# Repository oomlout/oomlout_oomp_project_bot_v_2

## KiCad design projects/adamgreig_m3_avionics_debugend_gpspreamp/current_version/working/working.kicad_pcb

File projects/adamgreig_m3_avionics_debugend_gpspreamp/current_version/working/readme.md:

# m3_avionics
 
## summary 
* id: adamgreig_m3_avionics_debugend_gpspreamp
* user: adamgreig
* name: m3_avionics
* board: debugend_gpspreamp
* repo: https://github.com/adamgreig/m3-avionics
* src_file_repo_kicad_pcb: m3debug/end_pcb/panel_with_gpspreamp/debugend_gpspreamp.kicad_pcb
* src_file_repo_kicad_pcb_link: https://github.com/adamgreig/m3-avionics/tree/master/m3debug/end_pcb/panel_with_gpspreamp/debugend_gpspreamp.kicad_pcb

* src_file_repo_sch: m3debug/end_pcb/m3debug_end.sch
* src_file_repo_sch_link: https://github.com/adamgreig/m3-avionics/tree/master/m3debug/end_pcb/m3debug_end.sch
* full details link: https://github.com/oomlout/oomlout_oomp_project_bot_v_2/tree/main/projects/adamgreig_m3_avionics_debugend_gpspreamp/current_version/working  

## pcb  

[board (pdf)](working.pdf)  

## working_bom
| Id | Designator | Footprint | Quantity | Designation | Supplier and ref |  | None | 
| --- | --- | --- | --- | --- | --- | --- | --- | 
| 1 | J1 | TFML-110-02-L-D | 1 | WEST TOP |  |  | [''] | 
| 2 | J2 | TFML-110-02-L-D | 1 | EAST TOP |  |  | [''] | 
| 3 | R1 | 0402 | 1 | 120 |  |  | [''] | 
| 4 | J5,J6,J7,J8 | SIL-254P-10 | 4 | CONN_01x10 |  |  | [''] | 
| 5 | C1 | 0402 | 1 | 1Âµ |  |  | [''] | 
| 6 | C2 | 0402 | 1 | 100n |  |  | [''] | 
| 7 | C3 | 0402 | 1 | 200p |  |  | [''] | 
| 8 | IC1 | DFN-6-EP-BGM | 1 | BGM1043N7 |  |  | [''] | 
| 9 | L1 | 0402 | 1 | 9n1 |  |  | [''] | 
| 10 | L2 | 0402 | 1 | 8n2 |  |  | [''] | 
| 11 | L3,L4,L5 | 0402 | 3 | 92n |  |  | [''] | 
| 12 | P2 | SMA-PTH | 1 | ANTENNA |  |  | [''] | 
| 13 | P3 | SMA-EDGE | 1 | RECEIVER |  |  | [''] | 
| 14 | J3 | SFML-110-02-L-D-LC | 1 | WEST BOT |  |  | [''] | 
| 15 | J4 | SFML-110-02-L-D-LC | 1 | EAST BOT |  |  | [''] |

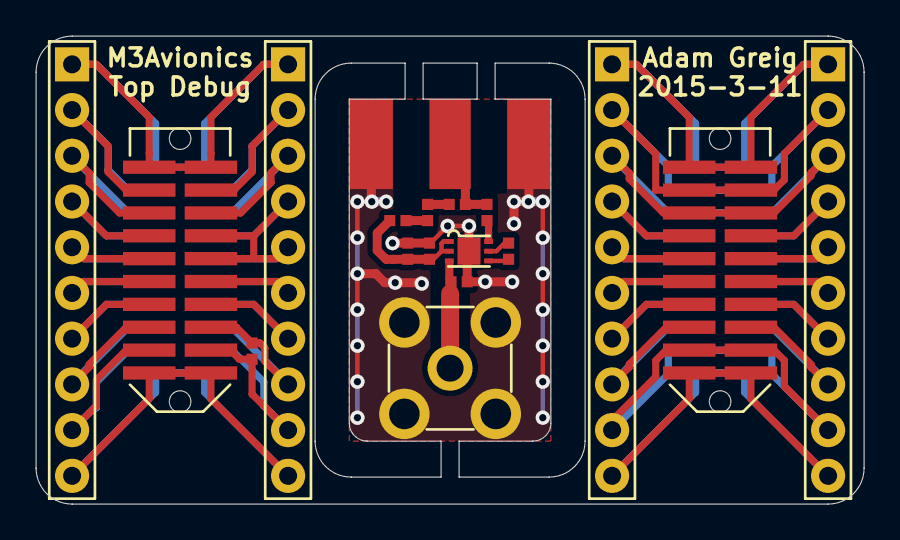
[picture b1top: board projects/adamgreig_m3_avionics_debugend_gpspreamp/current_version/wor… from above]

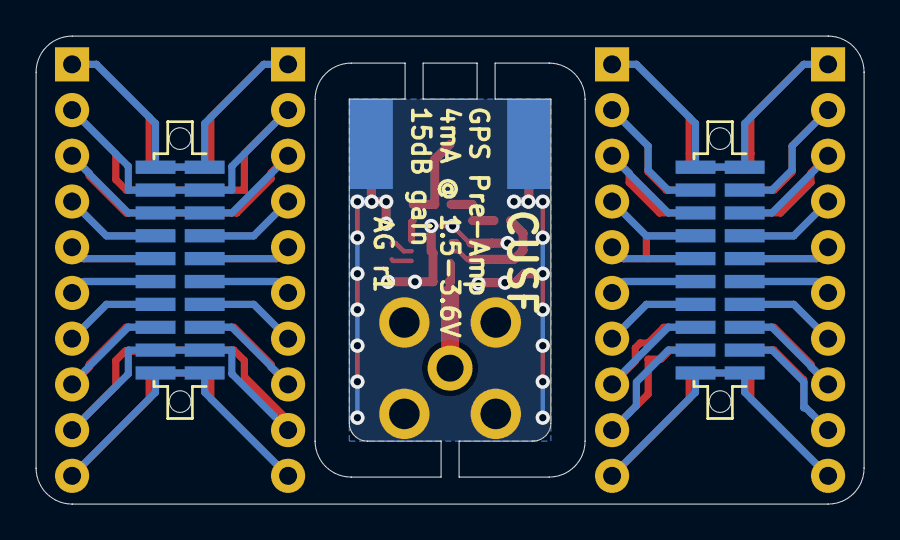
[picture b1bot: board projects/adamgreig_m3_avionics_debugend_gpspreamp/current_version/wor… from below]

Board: 2 copper layers, 46.0 x 26.0 mm, 20 parts (2 on the bottom side), 37 nets.

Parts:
C1: 1µ; 0402
C2: 100n; 0402
C3: 200p; 0402
IC1: BGM1043N7; DFN-6-EP-BGM
J1: WEST TOP; TFML-110-02-L-D
J2: EAST TOP; TFML-110-02-L-D
J3: WEST BOT; SFML-110-02-L-D-LC
J4: EAST BOT; SFML-110-02-L-D-LC
J5, J6, J7, J8: CONN_01x10; SIL-254P-10
L1: 9n1; 0402
L2: 8n2; 0402
L3, L4, L5: 92n; 0402
P2: ANTENNA; SMA-PTH
P3: RECEIVER; SMA-EDGE
R1: 120; 0402

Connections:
/3v3_AUX1: J1.13, J3.13, J5.7
/3v3_AUX2: J1.15, J3.15, J5.8
/3v3_DL: J1.11, J3.11, J5.6
/3v3_FC: J1.7, J3.7, J5.4
/3v3_IMU: J1.3, J3.3, J5.2
/3v3_PYRO: J1.9, J3.9, J5.5
/3v3_RADIO: J1.5, J3.5, J5.3
/5v_AUX1: J2.11, J4.11, J7.6
/5v_AUX2: J2.13, J4.13, J7.7
/5v_CAM: J2.15, J4.15, J7.8
/5v_CAN: J1.14, J3.14, J6.7
/5v_IMU: J2.9, J4.9, J7.5
/5v_RADIO: J2.7, J4.7, J7.4
/CAN+: J1.18, J3.18, J6.9, R1.1
/CAN-: J1.16, J3.16, J6.8, R1.2
/CHARGE: J2.17, J2.18, J4.17, J4.18, J7.9, J8.9
/JTCK: J1.6, J3.6, J6.3
/JTDI: J1.8, J1.10, J3.8, J3.10, J6.4, J6.5
/JTMS: J1.4, J3.4, J6.2
/PWR: J2.16, J4.16, J8.8
/PYRO1: J2.8, J4.8, J8.4
/PYRO2: J2.10, J4.10, J8.5
/PYRO3: J2.12, J4.12, J8.6
/PYRO4: J2.14, J4.14, J8.7
/PYRO_SI: J2.5, J2.6, J4.5, J4.6, J7.3, J8.3
/PYRO_SO: J2.3, J2.4, J4.3, J4.4, J7.2, J8.2
/RSVD1: J1.12, J3.12, J6.6
/RSVD2: J1.17, J3.17, J5.9
GND: C1.2, C2.2, IC1.EP, J1.1, J1.2, J1.19, J1.20, J2.1, J2.2, J2.19, J2.20, J3.1, J3.2, J3.19, J3.20, J4.1, J4.2, J4.19, J4.20, J5.1, J5.10, J6.1, J6.10, J7.1, J7.10, J8.1, J8.10, L1.2, P2.2, P3.2
unnamed: C1.1, C2.1, IC1.1, IC1.2, L3.1
unnamed: C3.1, IC1.6
unnamed: C3.2, L5.2, P3.1
unnamed: IC1.3, L1.1, P2.1
unnamed: IC1.4, L2.1
unnamed: IC1.5, L2.2
unnamed: L3.2, L4.1
unnamed: L4.2, L5.1

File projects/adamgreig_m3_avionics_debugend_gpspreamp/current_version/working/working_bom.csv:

"Id";"Designator";"Footprint";"Quantity";"Designation";"Supplier and ref";
1;"J1";"TFML-110-02-L-D";1;"WEST TOP";;;
2;"J2";"TFML-110-02-L-D";1;"EAST TOP";;;
3;"R1";"0402";1;"120";;;
4;"J5,J6,J7,J8";"SIL-254P-10";4;"CONN_01x10";;;
5;"C1";"0402";1;"1µ";;;
6;"C2";"0402";1;"100n";;;
7;"C3";"0402";1;"200p";;;
8;"IC1";"DFN-6-EP-BGM";1;"BGM1043N7";;;
9;"L1";"0402";1;"9n1";;;
10;"L2";"0402";1;"8n2";;;
11;"L3,L4,L5";"0402";3;"92n";;;
12;"P2";"SMA-PTH";1;"ANTENNA";;;
13;"P3";"SMA-EDGE";1;"RECEIVER";;;
14;"J3";"SFML-110-02-L-D-LC";1;"WEST BOT";;;
15;"J4";"SFML-110-02-L-D-LC";1;"EAST BOT";;;

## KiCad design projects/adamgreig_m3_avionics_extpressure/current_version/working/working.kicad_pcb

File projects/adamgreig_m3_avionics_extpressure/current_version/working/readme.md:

# m3_avionics
 
## summary 
* id: adamgreig_m3_avionics_extpressure
* user: adamgreig
* name: m3_avionics
* board: extpressure
* repo: https://github.com/adamgreig/m3-avionics
* src_file_repo_kicad_pcb: m3dl/extpressure/extpressure.kicad_pcb
* src_file_repo_kicad_pcb_link: https://github.com/adamgreig/m3-avionics/tree/master/m3dl/extpressure/extpressure.kicad_pcb

* src_file_repo_sch: m3dl/extpressure/extpressure.sch
* src_file_repo_sch_link: https://github.com/adamgreig/m3-avionics/tree/master/m3dl/extpressure/extpressure.sch
* full details link: https://github.com/oomlout/oomlout_oomp_project_bot_v_2/tree/main/projects/adamgreig_m3_avionics_extpressure/current_version/working  

## schematic  
  
[schematic (pdf)](working_schematic.pdf) 

## pcb  

[board (pdf)](working.pdf)  

## working_bom
| Id | Designator | Footprint | Quantity | Designation | Supplier and ref |  | None | 
| --- | --- | --- | --- | --- | --- | --- | --- | 
| 1 | P1 | TC2030-NL | 1 | SWD_TC |  |  | [''] | 
| 2 | IC1,IC4,IC3,IC2 | SP100 | 4 | SP100 |  |  | [''] | 
| 3 | J1 | S04B-PASK-2 | 1 | SERIAL |  |  | [''] | 
| 4 | IC5 | LQFP-32 | 1 | STM32F0xxKxTx |  |  | [''] | 
| 5 | D1 | 0603-LED | 1 | RED |  |  | [''] | 
| 6 | C3,C4,C1,C6,C7,C2 | 0402 | 6 | 100n |  |  | [''] | 
| 7 | C5 | 0402 | 1 | 4Âµ7 |  |  | [''] | 
| 8 | C8 | 0402 | 1 | 1Âµ |  |  | [''] | 
| 9 | C9 | 0402 | 1 | 10n |  |  | [''] | 
| 10 | R1,R2 | 0402 | 2 | 1k |  |  | [''] | 
| 11 | D2 | 0603-LED | 1 | GRN |  |  | [''] | 
| 12 | REF**,REF**,REF**,REF** | M3_MOUNT | 4 | M3_MOUNT |  |  | [''] | 
| 13 | D4,D5,D3 | 0402 | 3 | ESD_DIODE |  |  | [''] | 

## bom_schematic
| Ref | Qnty | Value | Cmp name | Footprint | Description | Vendor | DNP | 
| --- | --- | --- | --- | --- | --- | --- | --- | 
| C1, C2, C3, C4, C6, C7 | 6 | 100n | C | agg:0402 |  |  |  | 
| C5 | 1 | 4Âµ7 | C | agg:0402 |  |  |  | 
| C8 | 1 | 1Âµ | C | agg:0402 |  |  |  | 
| C9 | 1 | 10n | C | agg:0402 |  |  |  | 
| D1 | 1 | RED | LED | agg:0603-LED |  |  |  | 
| D2 | 1 | GRN | LED | agg:0603-LED |  |  |  | 
| D3, D4, D5 | 3 | ESD_DIODE | ESD_DIODE | agg:0402 |  |  |  | 
| IC1, IC2, IC3, IC4 | 4 | SP100 | SP100 | agg:SP100 |  |  |  | 
| IC5 | 1 | STM32F0xxKxTx | STM32F0xxKxTx | agg:LQFP-32 |  |  |  | 
| J1 | 1 | SERIAL | CONN_01x04 | agg:S04B-PASK-2 |  |  |  | 
| P1 | 1 | SWD_TC | SWD_TC | agg:TC2030-NL |  |  |  | 
| R1, R2 | 2 | 1k | R | agg:0402 |  |  |  |

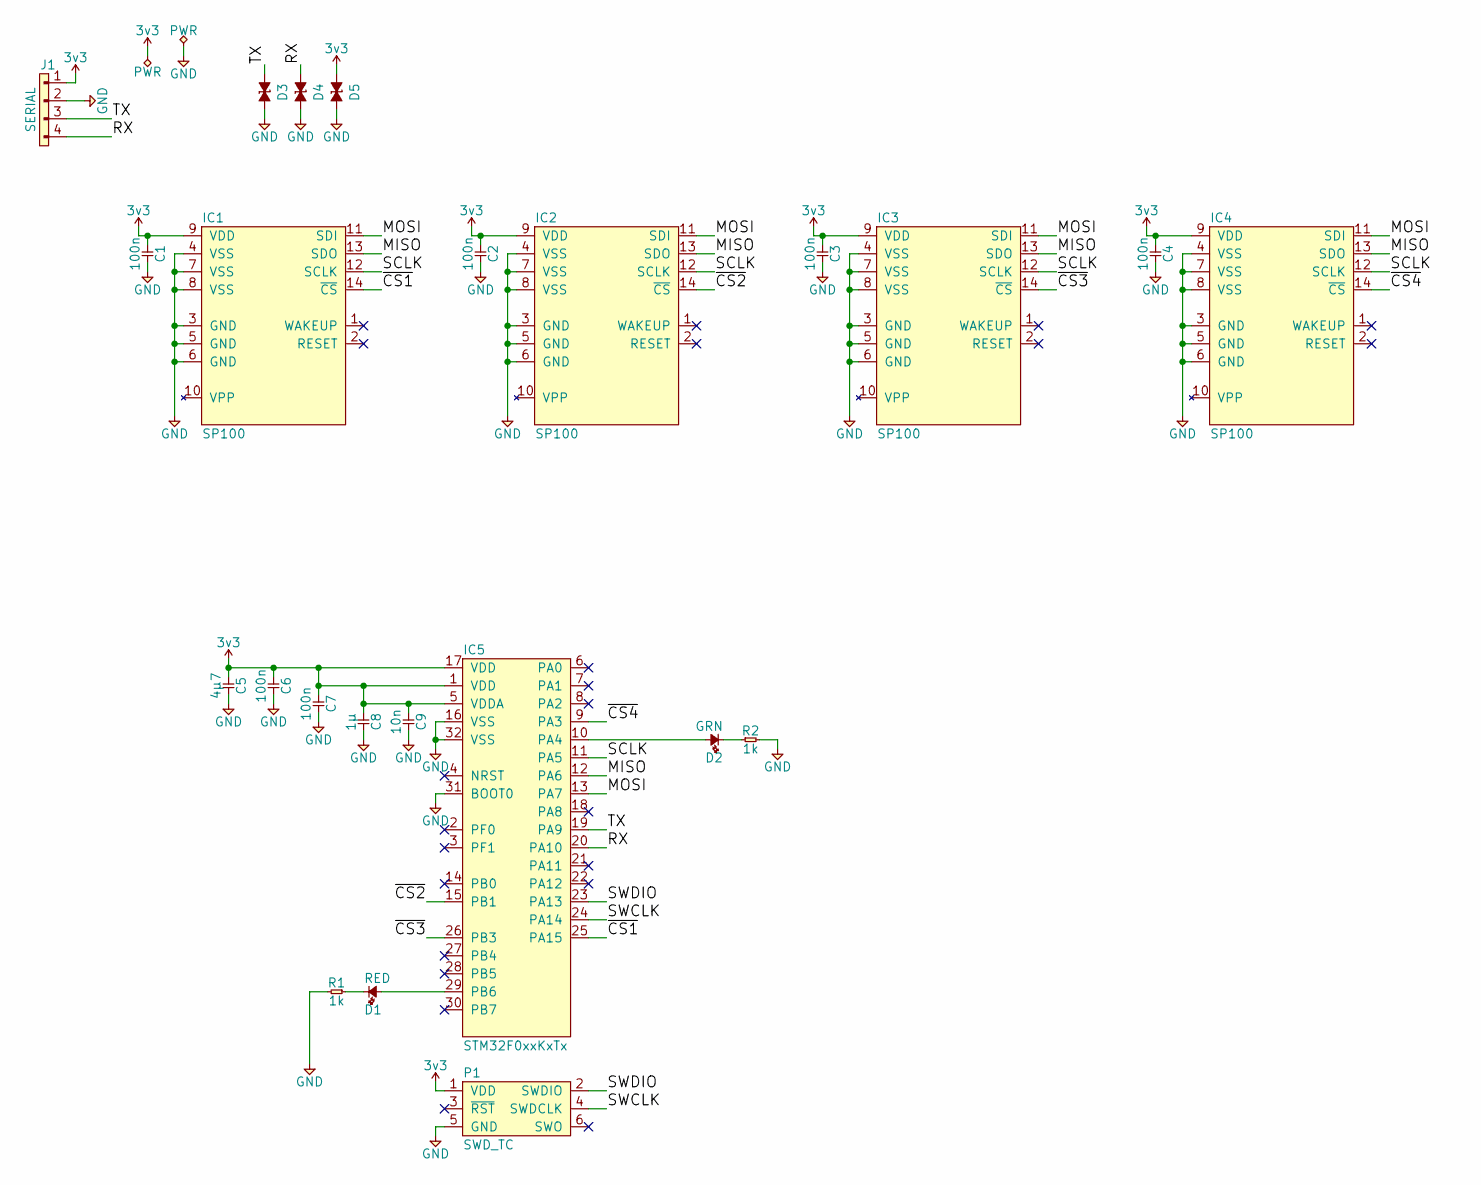
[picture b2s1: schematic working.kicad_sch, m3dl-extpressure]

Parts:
C1, C2, C3, C4, C6, C7: 100n; 0402; Farnell 2496771
C5: 4µ7; 0402; Farnell 2426952
C8: 1µ; 0402; Farnell 2496814
C9: 10n; 0402; Farnell 2210793
D1: RED; 0603-LED; Farnell 2290329
D2: GRN; 0603-LED; Farnell 2290328
D3, D4, D5: ESD_DIODE; 0402; Farnell 2368169
IC1, IC2, IC3, IC4: SP100; Farnell 1845345
IC5: STM32F0xxKxTx; LQFP-32; Farnell 2333141
J1: SERIAL; S04B-PASK-2; Farnell 1830749
P1: SWD_TC; TC2030-NL
R1, R2: 1k; 0402; Farnell 2447120

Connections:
3v3: C1.1, C2.1, C3.1, C4.1, C5.1, C6.1, C7.1, C8.1, C9.1, D5.1, IC1.9 (VDD), IC2.9 (VDD), IC3.9 (VDD), IC4.9 (VDD), IC5.1 (VDD), IC5.5 (VDDA), IC5.17 (VDD), J1.1, P1.1 (VDD)
/MISO: IC1.13 (SDO), IC2.13 (SDO), IC3.13 (SDO), IC4.13 (SDO), IC5.12 (PA6)
/MOSI: IC1.11 (SDI), IC2.11 (SDI), IC3.11 (SDI), IC4.11 (SDI), IC5.13 (PA7)
/RX: D4.1, IC5.20 (PA10), J1.4
/SCLK: IC1.12 (SCLK), IC2.12 (SCLK), IC3.12 (SCLK), IC4.12 (SCLK), IC5.11 (PA5)
/SWCLK: IC5.24 (PA14), P1.4 (SWDCLK)
/SWDIO: IC5.23 (PA13), P1.2 (SWDIO)
/TX: D3.1, IC5.19 (PA9), J1.3
/~CS1: IC1.14 (~CS), IC5.25 (PA15)
/~CS2: IC2.14 (~CS), IC5.15 (PB1)
/~CS3: IC3.14 (~CS), IC5.26 (PB3)
/~CS4: IC4.14 (~CS), IC5.9 (PA3)
GND: C1.2, C2.2, C3.2, C4.2, C5.2, C6.2, C7.2, C8.2, C9.2, D3.2, D4.2, D5.2, IC1.3 (GND), IC1.4 (VSS), IC1.5 (GND), IC1.6 (GND), IC1.7 (VSS), IC1.8 (VSS), IC2.3 (GND), IC2.4 (VSS), IC2.5 (GND), IC2.6 (GND), IC2.7 (VSS), IC2.8 (VSS), IC3.3 (GND), IC3.4 (VSS), IC3.5 (GND), IC3.6 (GND), IC3.7 (VSS), IC3.8 (VSS), IC4.3 (GND), IC4.4 (VSS), IC4.5 (GND), IC4.6 (GND), IC4.7 (VSS), IC4.8 (VSS), IC5.16 (VSS), IC5.31 (BOOT0), IC5.32 (VSS), J1.2, P1.5 (GND), R1.2, R2.2
unnamed: D1.1, R1.1
unnamed: D1.2, IC5.29 (PB6)
unnamed: D2.1, R2.1
unnamed: D2.2, IC5.10 (PA4)

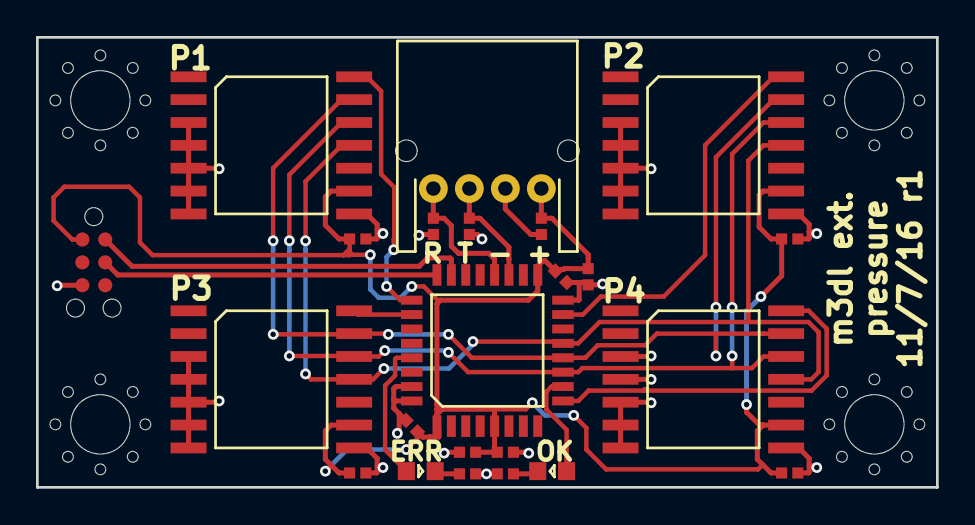
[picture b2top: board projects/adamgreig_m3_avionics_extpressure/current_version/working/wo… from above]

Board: 2 copper layers, 50.0 x 25.0 mm, 23 parts (0 on the bottom side), 17 nets.

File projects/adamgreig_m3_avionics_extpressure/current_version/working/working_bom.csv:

"Id";"Designator";"Footprint";"Quantity";"Designation";"Supplier and ref";
1;"P1";"TC2030-NL";1;"SWD_TC";;;
2;"IC1,IC4,IC3,IC2";"SP100";4;"SP100";;;
3;"J1";"S04B-PASK-2";1;"SERIAL";;;
4;"IC5";"LQFP-32";1;"STM32F0xxKxTx";;;
5;"D1";"0603-LED";1;"RED";;;
6;"C3,C4,C1,C6,C7,C2";"0402";6;"100n";;;
7;"C5";"0402";1;"4µ7";;;
8;"C8";"0402";1;"1µ";;;
9;"C9";"0402";1;"10n";;;
10;"R1,R2";"0402";2;"1k";;;
11;"D2";"0603-LED";1;"GRN";;;
12;"REF**,REF**,REF**,REF**";"M3_MOUNT";4;"M3_MOUNT";;;
13;"D4,D5,D3";"0402";3;"ESD_DIODE";;;

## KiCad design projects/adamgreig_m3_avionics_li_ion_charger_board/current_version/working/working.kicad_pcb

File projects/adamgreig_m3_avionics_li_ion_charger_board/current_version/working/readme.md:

# m3_avionics
 
## summary 
* id: adamgreig_m3_avionics_li_ion_charger_board
* user: adamgreig
* name: m3_avionics
* board: li_ion_charger_board
* repo: https://github.com/adamgreig/m3-avionics
* src_file_repo_kicad_pcb: m3psu/pcb/Li-Ion-Charger-Board/Li-Ion-Charger-Board.kicad_pcb
* src_file_repo_kicad_pcb_link: https://github.com/adamgreig/m3-avionics/tree/master/m3psu/pcb/Li-Ion-Charger-Board/Li-Ion-Charger-Board.kicad_pcb

* src_file_repo_sch: m3psu/pcb/Li-Ion-Charger-Board/Li-Ion-Charger-Board.sch
* src_file_repo_sch_link: https://github.com/adamgreig/m3-avionics/tree/master/m3psu/pcb/Li-Ion-Charger-Board/Li-Ion-Charger-Board.sch
* full details link: https://github.com/oomlout/oomlout_oomp_project_bot_v_2/tree/main/projects/adamgreig_m3_avionics_li_ion_charger_board/current_version/working  

## schematic  
  
[schematic (pdf)](working_schematic.pdf) 

## pcb  

[board (pdf)](working.pdf)  

## working_bom
| Id | Designator | Footprint | Quantity | Designation | Supplier and ref |  | None | 
| --- | --- | --- | --- | --- | --- | --- | --- | 
| 1 | J1 | TFML-110-02-L-D | 1 | WEST TOP |  |  | [''] | 
| 2 | J4 | TFML-110-02-L-D | 1 | EAST TOP |  |  | [''] | 
| 3 | J3 | SIL-254P-01 | 1 | TAP |  |  | [''] | 
| 4 | J7 | SIL-254P-01 | 1 | BAT+ |  |  | [''] | 
| 5 | J8 | SIL-254P-01 | 1 | BAT- |  |  | [''] | 
| 6 | C1,C2,C8,C10,C11,C14,C15,C16,C17 | 0402 | 9 | 100n |  |  | [''] | 
| 7 | C3,C13 | 0402 | 2 | 1Âµ |  |  | [''] | 
| 8 | C4,C7 | 0805 | 2 | 2Âµ2 |  |  | [''] | 
| 9 | C5,C6,C18,C19 | 1210 | 4 | 10Âµ |  |  | [''] | 
| 10 | C9 | 0603 | 1 | 1Âµ5 |  |  | [''] | 
| 11 | C12 | 0402 | 1 | 100p |  |  | [''] | 
| 12 | C20 | 0402 | 1 | 22p |  |  | [''] | 
| 13 | D3,D4 | SOD-323 | 2 | SCHOTTKY |  |  | [''] | 
| 14 | IC1 | QFN-32-EP-TI | 1 | BQ40Z60 |  |  | [''] | 
| 15 | L1 | SRP5030T | 1 | 2Âµ2 |  |  | [''] | 
| 16 | Q1 | PowerFLAT-5x6 | 1 | NFET2 |  |  | [''] | 
| 17 | Q2 | SOT-883-B | 1 | NFET |  |  | [''] | 
| 18 | Q4 | PowerPair-3x3 | 1 | SiZ340DT |  |  | [''] | 
| 19 | R1 | 0402 | 1 | 10K |  |  | [''] | 
| 20 | R2,R7,R9 | 0402 | 3 | 10M |  |  | [''] | 
| 21 | R3,R4,R8 | 0402 | 3 | 5K1 |  |  | [''] | 
| 22 | R10,R11,R15,R16 | 0402 | 4 | 100R |  |  | [''] | 
| 23 | R12 | 0402 | 1 | 100K |  |  | [''] | 
| 24 | R13 | 0402 | 1 | 2R |  |  | [''] | 
| 25 | R14,R19 | 0402 | 2 | 10R |  |  | [''] | 
| 26 | R17 | 0805 | 1 | 5m |  |  | [''] | 
| 27 | R18 | 0603 | 1 | 10m |  |  | [''] | 
| 28 | R20 | 0402 | 1 | 330K |  |  | [''] | 
| 29 | R21 | 0402 | 1 | 56K2 |  |  | [''] | 
| 30 | Q3 | SON2x2N | 1 | NFET_GDS |  |  | [''] | 
| 31 | J2 | SFML-110-02-L-D-LC | 1 | WEST BOT |  |  | [''] | 
| 32 | J5 | SFML-110-02-L-D-LC | 1 | EAST BOT |  |  | [''] | 
| 33 | J6 | SFML-105-02-L-D-LC | 1 | NORTH BOT |  |  | [''] | 

## bom_schematic
| Ref | Qnty | Value | Cmp name | Footprint | Description | Vendor | DNP | 
| --- | --- | --- | --- | --- | --- | --- | --- | 
| C1, C2, C8, C10, C11, C14, C15, C16, C17 | 9 | 100n | C | agg:0402 |  |  |  | 
| C3, C13 | 2 | 1Âµ | C | agg:0402 |  |  |  | 
| C4, C7 | 2 | 2Âµ2 | C | agg:0805 |  |  |  | 
| C5, C6, C18, C19 | 4 | 10Âµ | C | agg:1210 |  |  |  | 
| C9 | 1 | 1Âµ5 | C | agg:0603 |  |  |  | 
| C12 | 1 | 100p | C | agg:0402 |  |  |  | 
| C20 | 1 | 22p | C | agg:0402 |  |  |  | 
| D3, D4 | 2 | SCHOTTKY | SCHOTTKY | agg:SOD-323 |  |  |  | 
| IC1 | 1 | BQ40Z60 | BQ40Z60 | agg:QFN-32-EP-TI |  |  |  | 
| J1 | 1 | WEST TOP | CONN_02x10 | agg:TFML-110-02-L-D |  |  |  | 
| J2 | 1 | WEST BOT | CONN_02x10 | agg:SFML-110-02-L-D-LC |  |  |  | 
| J3 | 1 | TAP | CONN_01x01 | agg:SIL-254P-01 |  |  |  | 
| J4 | 1 | EAST TOP | CONN_02x10 | agg:TFML-110-02-L-D |  |  |  | 
| J5 | 1 | EAST BOT | CONN_02x10 | agg:SFML-110-02-L-D-LC |  |  |  | 
| J6 | 1 | NORTH BOT | CONN_02x05 | agg:SFML-105-02-L-D-LC |  |  |  | 
| J7 | 1 | BAT+ | CONN_01x01 | agg:SIL-254P-01 |  |  |  | 
| J8 | 1 | BAT- | CONN_01x01 | agg:SIL-254P-01 |  |  |  | 
| L1 | 1 | 2Âµ2 | L | agg:SRP5030T |  |  |  | 
| Q1 | 1 | NFET2 | NFET2 | agg:PowerFLAT-5x6 |  |  |  | 
| Q2 | 1 | NFET | NFET_GDS | agg:SOT-883-B |  |  |  | 
| Q3 | 1 | NFET_GDS | NFET_GDS | agg:SON2x2N |  |  |  | 
| Q4 | 1 | SiZ340DT | SiZ340DT | agg:PowerPair-3x3 |  |  |  | 
| R1 | 1 | 10K | R | agg:0402 |  |  |  | 
| R2, R7, R9 | 3 | 10M | R | agg:0402 |  |  |  | 
| R3, R4, R8 | 3 | 5K1 | R | agg:0402 |  |  |  | 
| R10, R11, R15, R16 | 4 | 100R | R | agg:0402 |  |  |  | 
| R12 | 1 | 100K | R | agg:0402 |  |  |  | 
| R13 | 1 | 2R | R | agg:0402 |  |  |  | 
| R14, R19 | 2 | 10R | R | agg:0402 |  |  |  | 
| R17 | 1 | 5m | R | agg:0805 |  |  |  | 
| R18 | 1 | 10m | R | agg:0603 |  |  |  | 
| R20 | 1 | 330K | R | agg:0402 |  |  |  | 
| R21 | 1 | 56K2 | R | agg:0402 |  |  |  |

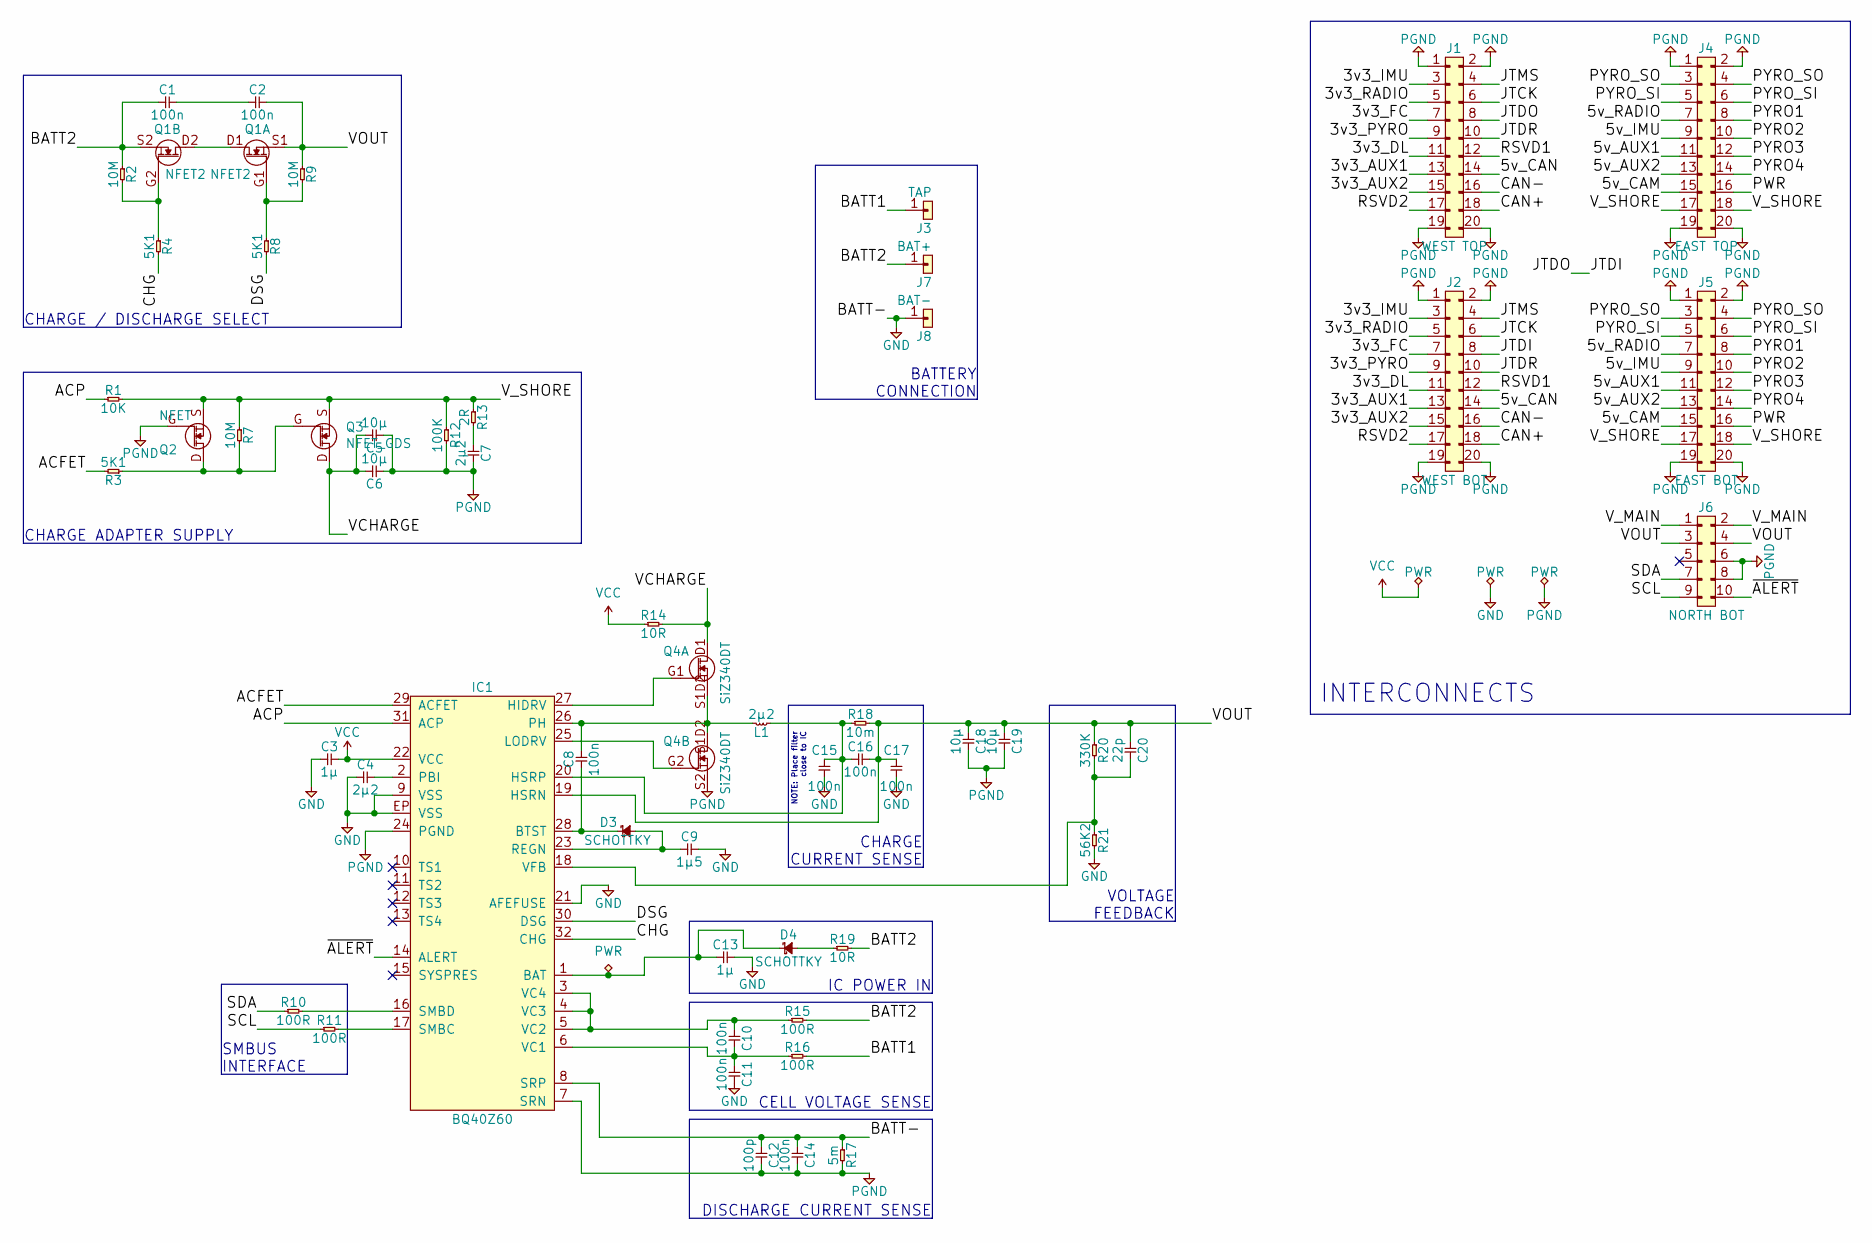
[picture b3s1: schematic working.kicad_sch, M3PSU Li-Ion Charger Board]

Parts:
C1, C2, C8, C10, C11, C14, C15, C16, C17: 100n; 0402; Farnell 2218856
C3, C13: 1µ; 0402; Farnell 2218855
C4, C7: 2µ2; 0805; Farnell 1657931
C5, C6, C18, C19: 10µ; 1210; Farnell 1845762
C9: 1µ5; 0603; Farnell 2211176
C12: 100p; 0402; Farnell 2496792
C20: 22p; 0402; Farnell 2496799
D3, D4: SCHOTTKY; SOD-323; Farnell 1459033
IC1: BQ40Z60; QFN-32-EP-TI; Farnell 2471154
J1: WEST TOP; TFML-110-02-L-D
J2: WEST BOT; SFML-110-02-L-D-LC
J3: TAP; SIL-254P-01
J4: EAST TOP; TFML-110-02-L-D
J5: EAST BOT; SFML-110-02-L-D-LC
J6: NORTH BOT; SFML-105-02-L-D-LC
J7: BAT+; SIL-254P-01
J8: BAT-; SIL-254P-01
L1: 2µ2; SRP5030T; Farnell 2309885
Q1: NFET2; PowerFLAT-5x6; Farnell 2098274
Q2: NFET; SOT-883-B; Farnell 2498598
Q3: NFET_GDS; SON2x2N; Farnell 2544998
Q4: SiZ340DT; PowerPair-3x3; Farnell 2422226
R1: 10K; 0402; Farnell 1469669
R2, R7, R9: 10M; 0402; Farnell 1469670
R3, R4, R8: 5K1; 0402; Farnell 1458805
R10, R11, R15, R16: 100R; 0402; Farnell 9239111
R12: 100K; 0402; Farnell 9239472
R13: 2R; 0402; Farnell 2059192
R14, R19: 10R; 0402; Farnell 1652742
R17: 5m; 0805; Farnell 2518218
R18: 10m; 0603; Farnell 2503038
R20: 330K; 0402; Farnell 2502450
R21: 56K2; 0402; Farnell 2059175

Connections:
/3v3_AUX1: J1.13, J2.13
/3v3_AUX2: J1.15, J2.15
/3v3_DL: J1.11, J2.11
/3v3_FC: J1.7, J2.7
/3v3_IMU: J1.3, J2.3
/3v3_PYRO: J1.9, J2.9
/3v3_RADIO: J1.5, J2.5
/5v_AUX1: J4.11, J5.11
/5v_AUX2: J4.13, J5.13
/5v_CAM: J4.15, J5.15
/5v_CAN: J1.14, J2.14
/5v_IMU: J4.9, J5.9
/5v_RADIO: J4.7, J5.7
/ACFET: IC1.29 (ACFET), R3.2
/ACP: IC1.31 (ACP), R1.1
/BATT1: J3.1, R16.2
/BATT2: C1.1, J7.1, Q1.S2 (S), R2.1, R15.2, R19.2
/CAN+: J1.18, J2.18
/CAN-: J1.16, J2.16
/CHG: IC1.32 (CHG), R4.2
/DSG: IC1.30 (DSG), R8.2
/JTCK: J1.6, J2.6
/JTDI: J1.8, J2.8
/JTDR: J1.10, J2.10
/JTMS: J1.4, J2.4
/PWR: J4.16, J5.16
/PYRO1: J4.8, J5.8
/PYRO2: J4.10, J5.10
/PYRO3: J4.12, J5.12
/PYRO4: J4.14, J5.14
/PYRO_SI: J4.5, J4.6, J5.5, J5.6
/PYRO_SO: J4.3, J4.4, J5.3, J5.4
/RSVD1: J1.12, J2.12
/RSVD2: J1.17, J2.17
/SCL: J6.9, R11.1
/SDA: J6.7, R10.1
/VCHARGE: C5.2, C6.2, Q3.D, Q4.D1 (S1D2), R14.2
/VOUT: C2.2, C16.2, C17.2, C18.1, C19.1, C20.1, IC1.19 (HSRN), J6.3, J6.4, Q1.S1 (S), R9.1, R18.2, R20.1
/V_MAIN: J6.1, J6.2
/V_SHORE: J4.17, J4.18, J5.17, J5.18, Q2.S, Q3.S, R1.2, R7.1, R12.1, R13.1
/~ALERT: IC1.14 (ALERT), J6.10
GND: C3.1, C4.1, C9.2, C11.2, C12.1, C13.2, C14.1, C15.1, C17.1, IC1.8 (SRP), IC1.9 (VSS), IC1.21 (AFEFUSE), IC1.EP (VSS), J8.1, R17.1, R21.2
unnamed: C1.2, C2.1
unnamed: C4.2, IC1.2 (PBI)
unnamed: C7.1, R13.2
unnamed: C8.1, D3.1, IC1.28 (BTST)
unnamed: C8.2, IC1.26 (PH), L1.2, Q4.S1D2
unnamed: C9.1, D3.2, IC1.23 (REGN)
unnamed: C10.1, IC1.3 (VC4), IC1.4 (VC3), IC1.5 (VC2), R15.1
unnamed: C10.2, C11.1, IC1.6 (VC1), R16.1
unnamed: C13.1, D4.1, IC1.1 (BAT)
unnamed: C15.2, C16.1, IC1.20 (HSRP), L1.1, R18.1
unnamed: C20.2, IC1.18 (VFB), R20.2, R21.1
unnamed: D4.2, R19.1
unnamed: IC1.16 (SMBD), R10.2
unnamed: IC1.17 (SMBC), R11.2
unnamed: IC1.25 (LODRV), Q4.G2
unnamed: IC1.27 (HIDRV), Q4.G1
unnamed: Q1.D1 (D), Q1.D2 (D)
unnamed: Q1.G1 (G), R8.1, R9.2
unnamed: Q1.G2 (G), R2.2, R4.1
unnamed: Q2.D, Q3.G, R3.1, R7.2
PGND: C5.1, C6.1, C7.2, C12.2, C14.2, C18.2, C19.2, IC1.7 (SRN), IC1.24 (PGND), J1.1, J1.2, J1.19, J1.20, J2.1, J2.2, J2.19, J2.20, J4.1, J4.2, J4.19, J4.20, J5.1, J5.2, J5.19, J5.20, J6.6, J6.8, Q2.G, Q4.S2, R12.2, R17.2
VCC: C3.2, IC1.22 (VCC), R14.1

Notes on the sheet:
SMBUS INTERFACE
CELL VOLTAGE SENSE
IC POWER IN
NOTE: Place filter close to IC
VOLTAGE FEEDBACK
INTERCONNECTS
CHARGE CURRENT SENSE
DISCHARGE CURRENT SENSE
CHARGE ADAPTER SUPPLY
CHARGE / DISCHARGE SELECT
BATTERY CONNECTION

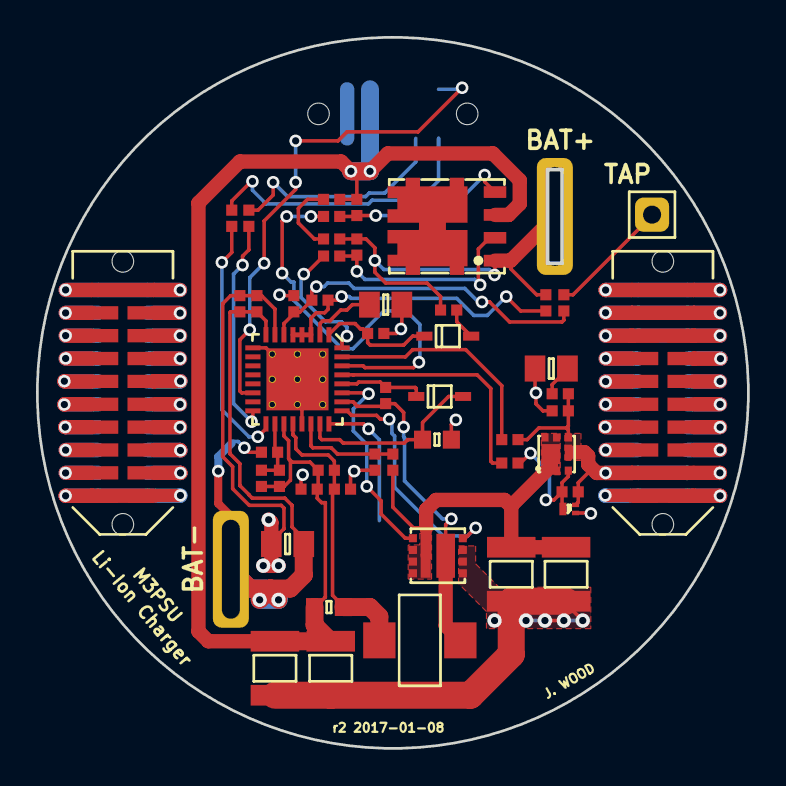
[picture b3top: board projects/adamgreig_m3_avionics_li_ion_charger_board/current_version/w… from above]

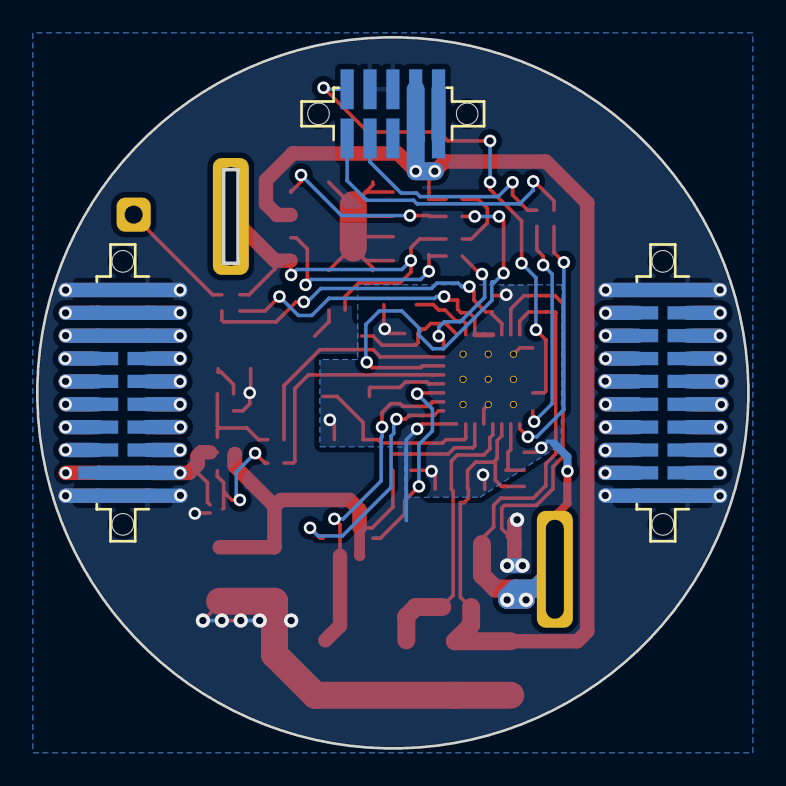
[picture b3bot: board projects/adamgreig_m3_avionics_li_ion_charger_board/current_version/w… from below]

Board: 2 copper layers, 39.5 x 39.5 mm, 55 parts (3 on the bottom side), 64 nets.

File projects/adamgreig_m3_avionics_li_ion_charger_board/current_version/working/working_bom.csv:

"Id";"Designator";"Footprint";"Quantity";"Designation";"Supplier and ref";
1;"J1";"TFML-110-02-L-D";1;"WEST TOP";;;
2;"J4";"TFML-110-02-L-D";1;"EAST TOP";;;
3;"J3";"SIL-254P-01";1;"TAP";;;
4;"J7";"SIL-254P-01";1;"BAT+";;;
5;"J8";"SIL-254P-01";1;"BAT-";;;
6;"C1,C2,C8,C10,C11,C14,C15,C16,C17";"0402";9;"100n";;;
7;"C3,C13";"0402";2;"1µ";;;
8;"C4,C7";"0805";2;"2µ2";;;
9;"C5,C6,C18,C19";"1210";4;"10µ";;;
10;"C9";"0603";1;"1µ5";;;
11;"C12";"0402";1;"100p";;;
12;"C20";"0402";1;"22p";;;
13;"D3,D4";"SOD-323";2;"SCHOTTKY";;;
14;"IC1";"QFN-32-EP-TI";1;"BQ40Z60";;;
15;"L1";"SRP5030T";1;"2µ2";;;
16;"Q1";"PowerFLAT-5x6";1;"NFET2";;;
17;"Q2";"SOT-883-B";1;"NFET";;;
18;"Q4";"PowerPair-3x3";1;"SiZ340DT";;;
19;"R1";"0402";1;"10K";;;
20;"R2,R7,R9";"0402";3;"10M";;;
21;"R3,R4,R8";"0402";3;"5K1";;;
22;"R10,R11,R15,R16";"0402";4;"100R";;;
23;"R12";"0402";1;"100K";;;
24;"R13";"0402";1;"2R";;;
25;"R14,R19";"0402";2;"10R";;;
26;"R17";"0805";1;"5m";;;
27;"R18";"0603";1;"10m";;;
28;"R20";"0402";1;"330K";;;
29;"R21";"0402";1;"56K2";;;
30;"Q3";"SON2x2N";1;"NFET_GDS";;;
31;"J2";"SFML-110-02-L-D-LC";1;"WEST BOT";;;
32;"J5";"SFML-110-02-L-D-LC";1;"EAST BOT";;;
33;"J6";"SFML-105-02-L-D-LC";1;"NORTH BOT";;;

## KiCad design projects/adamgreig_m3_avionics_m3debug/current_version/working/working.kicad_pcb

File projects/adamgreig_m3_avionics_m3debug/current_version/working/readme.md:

# m3_avionics
 
## summary 
* id: adamgreig_m3_avionics_m3debug
* user: adamgreig
* name: m3_avionics
* board: m3debug
* repo: https://github.com/adamgreig/m3-avionics
* src_file_repo_kicad_pcb: m3debug/pcb/m3debug.kicad_pcb
* src_file_repo_kicad_pcb_link: https://github.com/adamgreig/m3-avionics/tree/master/m3debug/pcb/m3debug.kicad_pcb

* src_file_repo_sch: m3debug/pcb/m3debug.sch
* src_file_repo_sch_link: https://github.com/adamgreig/m3-avionics/tree/master/m3debug/pcb/m3debug.sch
* full details link: https://github.com/oomlout/oomlout_oomp_project_bot_v_2/tree/main/projects/adamgreig_m3_avionics_m3debug/current_version/working  

## schematic  
  
[schematic (pdf)](working_schematic.pdf) 

## pcb  

[board (pdf)](working.pdf)  

## working_bom
| Id | Designator | Footprint | Quantity | Designation | Supplier and ref |  | None | 
| --- | --- | --- | --- | --- | --- | --- | --- | 
| 1 | C1,C2 | 0402 | 2 | 10p |  |  | [''] | 
| 2 | C3 | 0402 | 1 | 4Âµ7 |  |  | [''] | 
| 3 | C4,C5,C7,C8,C9,C12 | 0402 | 6 | 100n |  |  | [''] | 
| 4 | C6 | 0402 | 1 | 1Âµ |  |  | [''] | 
| 5 | C10,C11 | 0402 | 2 | 2Âµ2 |  |  | [''] | 
| 6 | C13,C15 | 0603 | 2 | 2Âµ2 |  |  | [''] | 
| 7 | C14 | 0402 | 1 | 1n |  |  | [''] | 
| 8 | C16,C17 | 0603 | 2 | 10Âµ |  |  | [''] | 
| 9 | D1,D2 | 0603-LED | 2 | YLW |  |  | [''] | 
| 10 | D3,D4,D5,D6,D7,D8 | 0603-LED | 6 | RED |  |  | [''] | 
| 11 | D9,D10,D11,D12 | 0603-LED | 4 | GRN |  |  | [''] | 
| 12 | IC1 | LQFP-64 | 1 | STM32F405RxTx |  |  | [''] | 
| 13 | IC2 | DFN-8-EP-MICROCHIP | 1 | MCP2562 |  |  | [''] | 
| 14 | IC3 | MSOP-8 | 1 | ADP3335 |  |  | [''] | 
| 15 | J1 | TFML-110-02-L-D | 1 | WEST TOP |  |  | [''] | 
| 16 | J3 | TFML-110-02-L-D | 1 | EAST TOP |  |  | [''] | 
| 17 | J5 | S02B-PASK-2 | 1 | PYRO_SUPPLY |  |  | [''] | 
| 18 | J6 | DIL-254P-08 | 1 | PYROS |  |  | [''] | 
| 19 | J8 | S02B-PASK-2 | 1 | CHARGE |  |  | [''] | 
| 20 | J9 | MICROUSB_MOLEX_47589-0001 | 1 | MICROUSB |  |  | [''] | 
| 21 | J10 | DIL-254P-10 | 1 | 5V_SUPPLY |  |  | [''] | 
| 22 | J12 | DIL-254P-14 | 1 | 3V3_SUPPLY |  |  | [''] | 
| 23 | P1 | TC2030-NL | 1 | SWD_TC |  |  | [''] | 
| 24 | R1,R2,R3,R4,R9,R10,R11,R12,R13,R14,R15,R16,R17 | 0402 | 13 | 1k |  |  | [''] | 
| 25 | R5 | 0402 | 1 | 100 |  |  | [''] | 
| 26 | R6 | 0402 | 1 | 120 |  |  | [''] | 
| 27 | R7 | 0402 | 1 | 4k7 |  |  | [''] | 
| 28 | R8 | 0402 | 1 | 10k |  |  | [''] | 
| 29 | Y1 | XTAL-20x16 | 1 | 26M |  |  | [''] | 
| 30 | J7 | SIL-254P-02 | 1 | PYRO_ARM |  |  | [''] | 
| 31 | J11 | SIL-254P-02 | 1 | CAN_SUPPLY |  |  | [''] | 
| 32 | J13 | SIL-254P-02 | 1 | PWRSW |  |  | [''] | 
| 33 | J14 | SIL-254P-04 | 1 | GND |  |  | [''] | 
| 34 | G***,G*** | cusf_logo_full | 2 | LOGO |  |  | [''] | 
| 35 | J2 | SFML-110-02-L-D-LC | 1 | WEST BOT |  |  | [''] | 
| 36 | J4 | SFML-110-02-L-D-LC | 1 | EAST BOT |  |  | [''] | 

## bom_schematic
| Ref | Qnty | Value | Cmp name | Footprint | Description | Vendor | DNP | 
| --- | --- | --- | --- | --- | --- | --- | --- | 
| C1, C2 | 2 | 10p | C | agg:0402 |  |  |  | 
| C3 | 1 | 4Âµ7 | C | agg:0402 |  |  |  | 
| C4, C5, C7, C8, C9, C12 | 6 | 100n | C | agg:0402 |  |  |  | 
| C6 | 1 | 1Âµ | C | agg:0402 |  |  |  | 
| C10, C11 | 2 | 2Âµ2 | C | agg:0402 |  |  |  | 
| C13, C15 | 2 | 2Âµ2 | C | agg:0603 |  |  |  | 
| C14 | 1 | 1n | C | agg:0402 |  |  |  | 
| C16, C17 | 2 | 10Âµ | C | agg:0603 |  |  |  | 
| D1, D2 | 2 | YLW | LED | agg:0603-LED |  |  |  | 
| D3, D4, D5, D6, D7, D8 | 6 | RED | LED | agg:0603-LED |  |  |  | 
| D9, D10, D11, D12 | 4 | GRN | LED | agg:0603-LED |  |  |  | 
| IC1 | 1 | STM32F405RxTx | STM32F405RxTx | agg:LQFP-64 |  |  |  | 
| IC2 | 1 | MCP2562 | MCP2562 | agg:DFN-8-EP-MICROCHIP |  |  |  | 
| IC3 | 1 | ADP3335 | ADP3335 | agg:MSOP-8 |  |  |  | 
| J1 | 1 | WEST TOP | CONN_02x10 | agg:TFML-110-02-L-D |  |  |  | 
| J2 | 1 | WEST BOT | CONN_02x10 | agg:SFML-110-02-L-D-LC |  |  |  | 
| J3 | 1 | EAST TOP | CONN_02x10 | agg:TFML-110-02-L-D |  |  |  | 
| J4 | 1 | EAST BOT | CONN_02x10 | agg:SFML-110-02-L-D-LC |  |  |  | 
| J5 | 1 | PYRO_SUPPLY | CONN_01x02 | agg:S02B-PASK-2 |  |  |  | 
| J6 | 1 | PYROS | CONN_02x04 | agg:DIL-254P-08 |  |  |  | 
| J7 | 1 | PYRO_ARM | CONN_02x01 | agg:SIL-254P-02 |  |  |  | 
| J8 | 1 | CHARGE | CONN_01x02 | agg:S02B-PASK-2 |  |  |  | 
| J9 | 1 | MICROUSB | MICROUSB | agg:MICROUSB_MOLEX_47589-0001 |  |  |  | 
| J10 | 1 | 5V_SUPPLY | CONN_02x05 | agg:DIL-254P-10 |  |  |  | 
| J11 | 1 | CAN_SUPPLY | CONN_02x01 | agg:SIL-254P-02 |  |  |  | 
| J12 | 1 | 3V3_SUPPLY | CONN_02x07 | agg:DIL-254P-14 |  |  |  | 
| J13 | 1 | PWRSW | CONN_02x01 | agg:SIL-254P-02 |  |  |  | 
| J14 | 1 | GND | CONN_01x04 | agg:SIL-254P-04 |  |  |  | 
| P1 | 1 | SWD_TC | SWD_TC | agg:TC2030-NL |  |  |  | 
| R1, R2, R3, R4, R9, R10, R11, R12, R13, R14, R15, R16, R17 | 13 | 1k | R | agg:0402 |  |  |  | 
| R5 | 1 | 100 | R | agg:0402 |  |  |  | 
| R6 | 1 | 120 | R | agg:0402 |  |  |  | 
| R7 | 1 | 4k7 | R | agg:0402 |  |  |  | 
| R8 | 1 | 10k | R | agg:0402 |  |  |  | 
| X1 | 1 | 2x3 conn | PART |  |  |  |  | 
| X2 | 1 | jumper | PART |  |  |  |  | 
| Y1 | 1 | 26M | SMD_XTAL | agg:XTAL-20x16 |  |  |  |

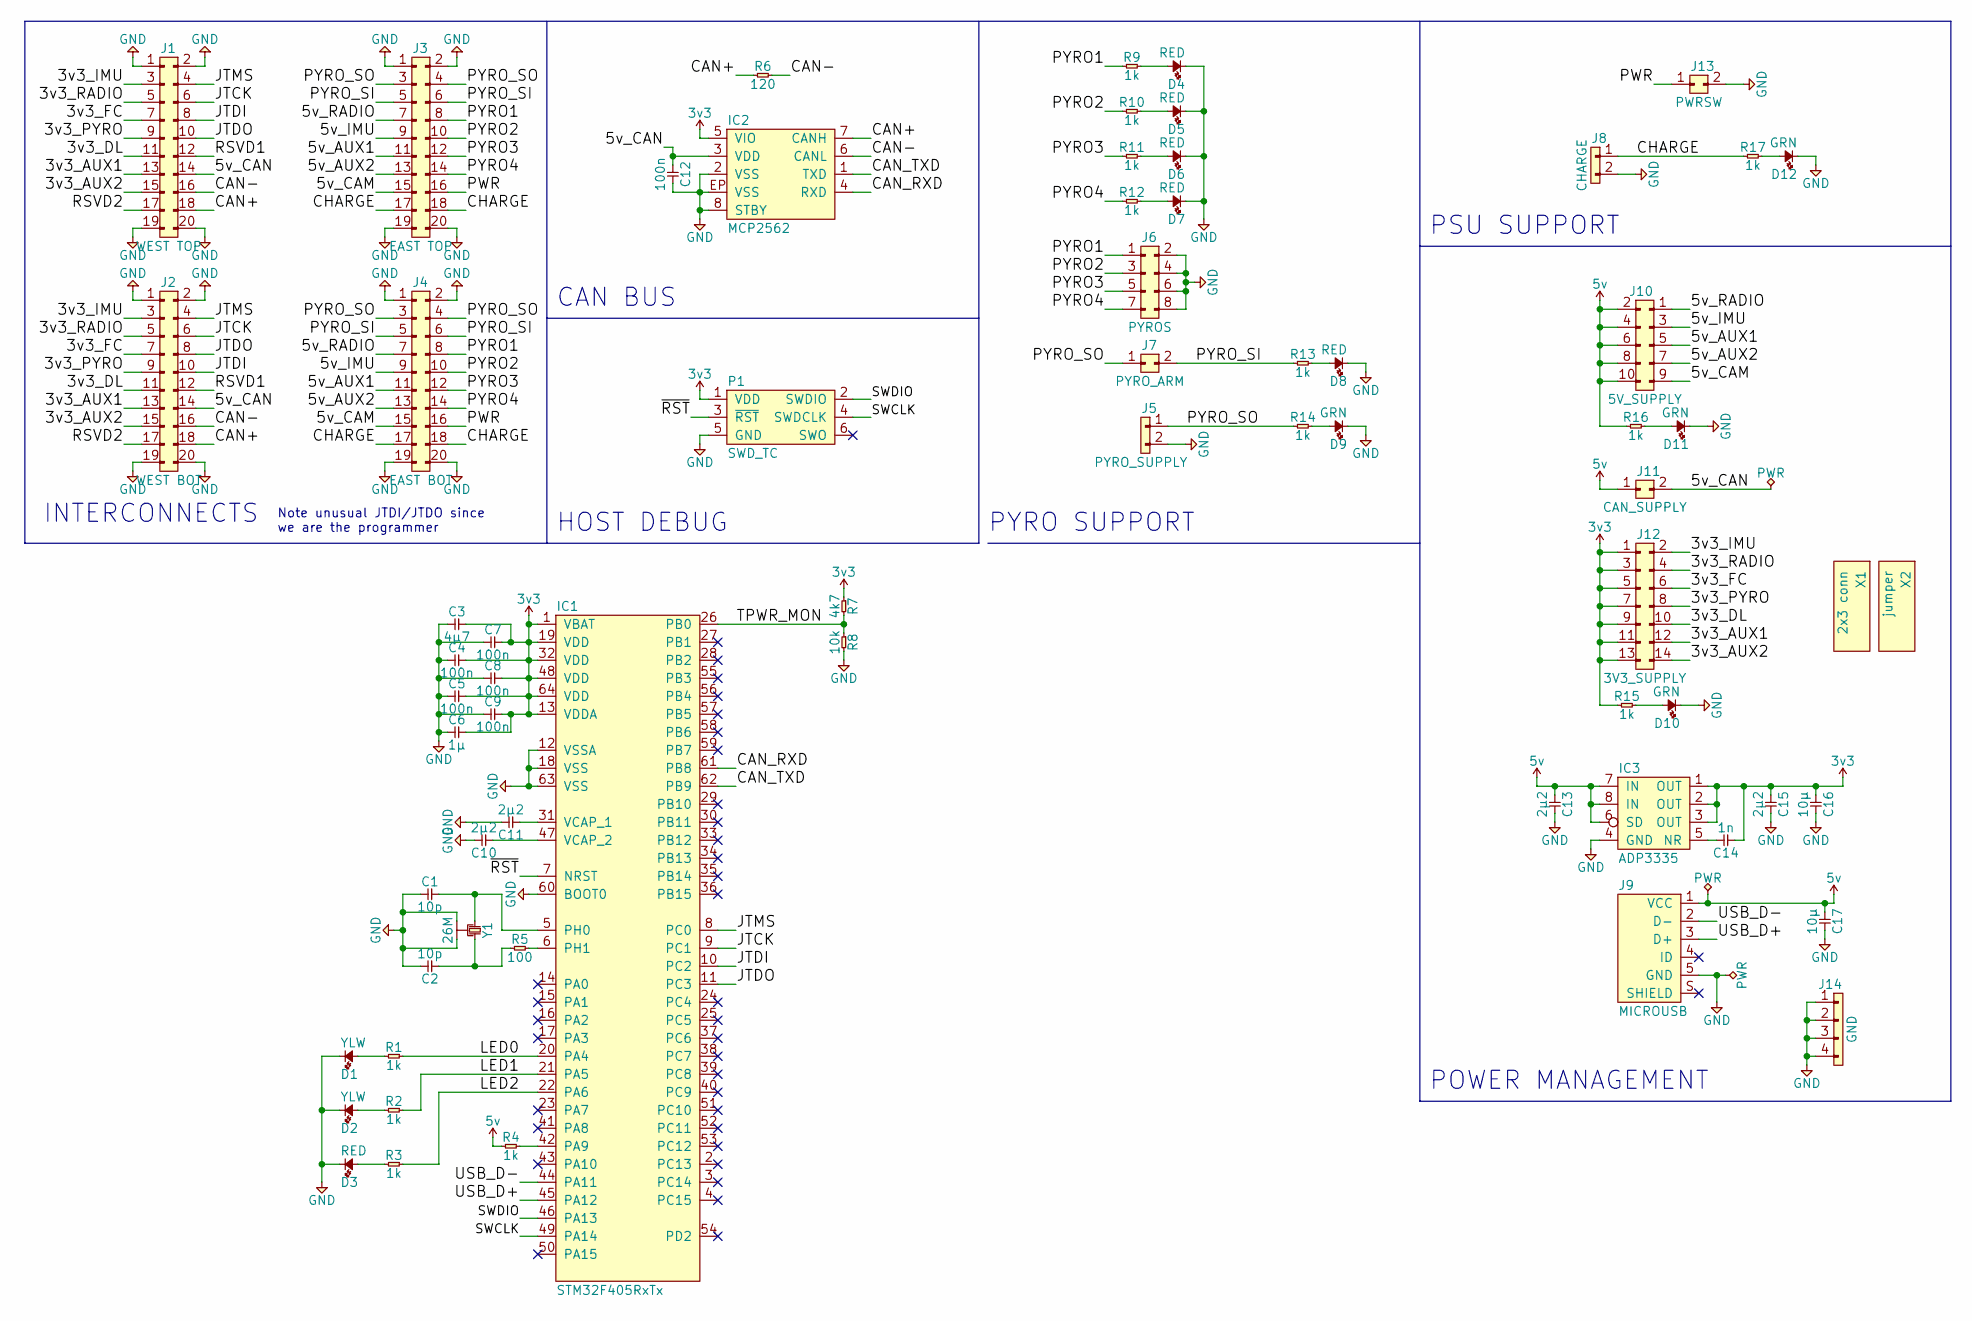
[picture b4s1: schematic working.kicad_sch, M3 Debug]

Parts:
C1, C2: 10p; 0402; Farnell 2496790
C3: 4µ7; 0402; Farnell 2426952
C4, C5, C7, C8, C9, C12: 100n; 0402; Farnell 2496771
C6: 1µ; 0402; Farnell 2496814
C10, C11: 2µ2; 0402; Farnell 2362088
C13, C15: 2µ2; 0603; Farnell 2496923
C14: 1n; 0402; Farnell 2496767
C16, C17: 10µ; 0603; Farnell 2456110
D1, D2: YLW; 0603-LED; Farnell 2290330
D3, D4, D5, D6, D7, D8: RED; 0603-LED; Farnell 2290329
D9, D10, D11, D12: GRN; 0603-LED; Farnell 2290328
IC1: STM32F405RxTx; LQFP-64; Farnell 2064363
IC2: MCP2562; DFN-8-EP-MICROCHIP; Farnell 2448755
IC3: ADP3335; MSOP-8; Farnell 2067775
J1: WEST TOP; TFML-110-02-L-D
J2: WEST BOT; SFML-110-02-L-D-LC
J3: EAST TOP; TFML-110-02-L-D
J4: EAST BOT; SFML-110-02-L-D-LC
J5: PYRO_SUPPLY; S02B-PASK-2; Farnell 1830747
J6: PYROS; DIL-254P-08; Farnell 1022232
J7: PYRO_ARM; SIL-254P-02; Farnell 1022245
J8: CHARGE; S02B-PASK-2; Farnell 1830747
J9: MICROUSB; MICROUSB_MOLEX_47589-0001; Farnell 1568023
J10: 5V_SUPPLY; DIL-254P-10; Farnell 1022235
J11: CAN_SUPPLY; SIL-254P-02; Farnell 1022245
J12: 3V3_SUPPLY; DIL-254P-14; Farnell 1022232
J13: PWRSW; SIL-254P-02; Farnell 1022245
J14: GND; SIL-254P-04; Farnell 1022250
P1: SWD_TC; TC2030-NL
R1, R2, R3, R4, R9, R10, R11, R12, R13, R14, R15, R16, R17: 1k; 0402; Farnell 9232761
R5: 100; 0402; Farnell 9239111
R6: 120; 0402; Farnell 2072575
R7: 4k7; 0402; Farnell 1358060
R8: 10k; 0402; Farnell 1358069
X1: 2x3 conn; Farnell 1022230
X2: jumper; Farnell 2396303
Y1: 26M; XTAL-20x16; Farnell 2506952

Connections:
3v3: C3.2, C4.2, C5.2, C6.2, C7.2, C8.2, C9.2, C14.1, C15.1, C16.1, IC1.1 (VBAT), IC1.13 (VDDA), IC1.19 (VDD), IC1.32 (VDD), IC1.48 (VDD), IC1.64 (VDD), IC2.5 (VIO), IC3.1 (OUT), IC3.2 (OUT), IC3.3 (OUT), J12.1, J12.3, J12.5, J12.7, J12.9, J12.11, J12.13, P1.1 (VDD), R7.1, R15.1
5v: C13.1, C17.1, IC3.6 (SD), IC3.7 (IN), IC3.8 (IN), J9.1 (VCC), J10.2, J10.4, J10.6, J10.8, J10.10, J11.1, R4.1, R16.1
/3v3_AUX1: J1.13, J2.13, J12.12
/3v3_AUX2: J1.15, J2.15, J12.14
/3v3_DL: J1.11, J2.11, J12.10
/3v3_FC: J1.7, J2.7, J12.6
/3v3_IMU: J1.3, J2.3, J12.2
/3v3_PYRO: J1.9, J2.9, J12.8
/3v3_RADIO: J1.5, J2.5, J12.4
/5v_AUX1: J3.11, J4.11, J10.5
/5v_AUX2: J3.13, J4.13, J10.7
/5v_CAM: J3.15, J4.15, J10.9
/5v_CAN: C12.1, IC2.3 (VDD), J1.14, J2.14, J11.2
/5v_IMU: J3.9, J4.9, J10.3
/5v_RADIO: J3.7, J4.7, J10.1
/CAN+: IC2.7 (CANH), J1.18, J2.18, R6.1
/CAN-: IC2.6 (CANL), J1.16, J2.16, R6.2
/CAN_RXD: IC1.61 (PB8), IC2.4 (RXD)
/CAN_TXD: IC1.62 (PB9), IC2.1 (TXD)
/CHARGE: J3.17, J3.18, J4.17, J4.18, J8.1, R17.1
/JTCK: IC1.9 (PC1), J1.6, J2.6
/JTDI: IC1.10 (PC2), J1.8, J2.10
/JTDO: IC1.11 (PC3), J1.10, J2.8
/JTMS: IC1.8 (PC0), J1.4, J2.4
/LED0: IC1.20 (PA4), R1.1
/LED1: IC1.21 (PA5), R2.1
/LED2: IC1.22 (PA6), R3.1
/PWR: J3.16, J4.16, J13.1
/PYRO1: J3.8, J4.8, J6.1, R9.1
/PYRO2: J3.10, J4.10, J6.3, R10.1
/PYRO3: J3.12, J4.12, J6.5, R11.1
/PYRO4: J3.14, J4.14, J6.7, R12.1
/PYRO_SI: J3.5, J3.6, J4.5, J4.6, J7.2, R13.1
/PYRO_SO: J3.3, J3.4, J4.3, J4.4, J5.1, J7.1, R14.1
/RSVD1: J1.12, J2.12
/RSVD2: J1.17, J2.17
/SWCLK: IC1.49 (PA14), P1.4 (SWDCLK)
/SWDIO: IC1.46 (PA13), P1.2 (SWDIO)
/TPWR_MON: IC1.26 (PB0), R7.2, R8.1
/USB_D+: IC1.45 (PA12), J9.3 (D+)
/USB_D-: IC1.44 (PA11), J9.2 (D-)
/~RST: IC1.7 (NRST), P1.3 (~RST)
GND: C1.1, C2.2, C3.1, C4.1, C5.1, C6.1, C7.1, C8.1, C9.1, C10.2, C11.2, C12.2, C13.2, C15.2, C16.2, C17.2, D1.1, D2.1, D3.1, D4.1, D5.1, D6.1, D7.1, D8.1, D9.1, D10.1, D11.1, D12.1, IC1.12 (VSSA), IC1.18 (VSS), IC1.60 (BOOT0), IC1.63 (VSS), IC2.2 (VSS), IC2.8 (STBY), IC2.EP (VSS), IC3.4 (GND), J1.1, J1.2, J1.19, J1.20, J2.1, J2.2, J2.19, J2.20, J3.1, J3.2, J3.19, J3.20, J4.1, J4.2, J4.19, J4.20, J5.2, J6.2, J6.4, J6.6, J6.8, J8.2, J9.5 (GND), J13.2, J14.1, J14.2, J14.3, J14.4, P1.5 (GND), R8.2, Y1.2, Y1.4
unnamed: C1.2, IC1.5 (PH0), Y1.1
unnamed: C2.1, R5.1, Y1.3
unnamed: C10.1, IC1.47 (VCAP_2)
unnamed: C11.1, IC1.31 (VCAP_1)
unnamed: C14.2, IC3.5 (NR)
unnamed: D1.2, R1.2
unnamed: D2.2, R2.2
unnamed: D3.2, R3.2
unnamed: D4.2, R9.2
unnamed: D5.2, R10.2
unnamed: D6.2, R11.2
unnamed: D7.2, R12.2
unnamed: D8.2, R13.2
unnamed: D9.2, R14.2
unnamed: D10.2, R15.2
unnamed: D11.2, R16.2
unnamed: D12.2, R17.2
unnamed: IC1.6 (PH1), R5.2
unnamed: IC1.42 (PA9), R4.2

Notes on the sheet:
Note unusual JTDI/JTDO since we are the programmer
POWER MANAGEMENT
PYRO SUPPORT
CAN BUS
PSU SUPPORT
HOST DEBUG
INTERCONNECTS
